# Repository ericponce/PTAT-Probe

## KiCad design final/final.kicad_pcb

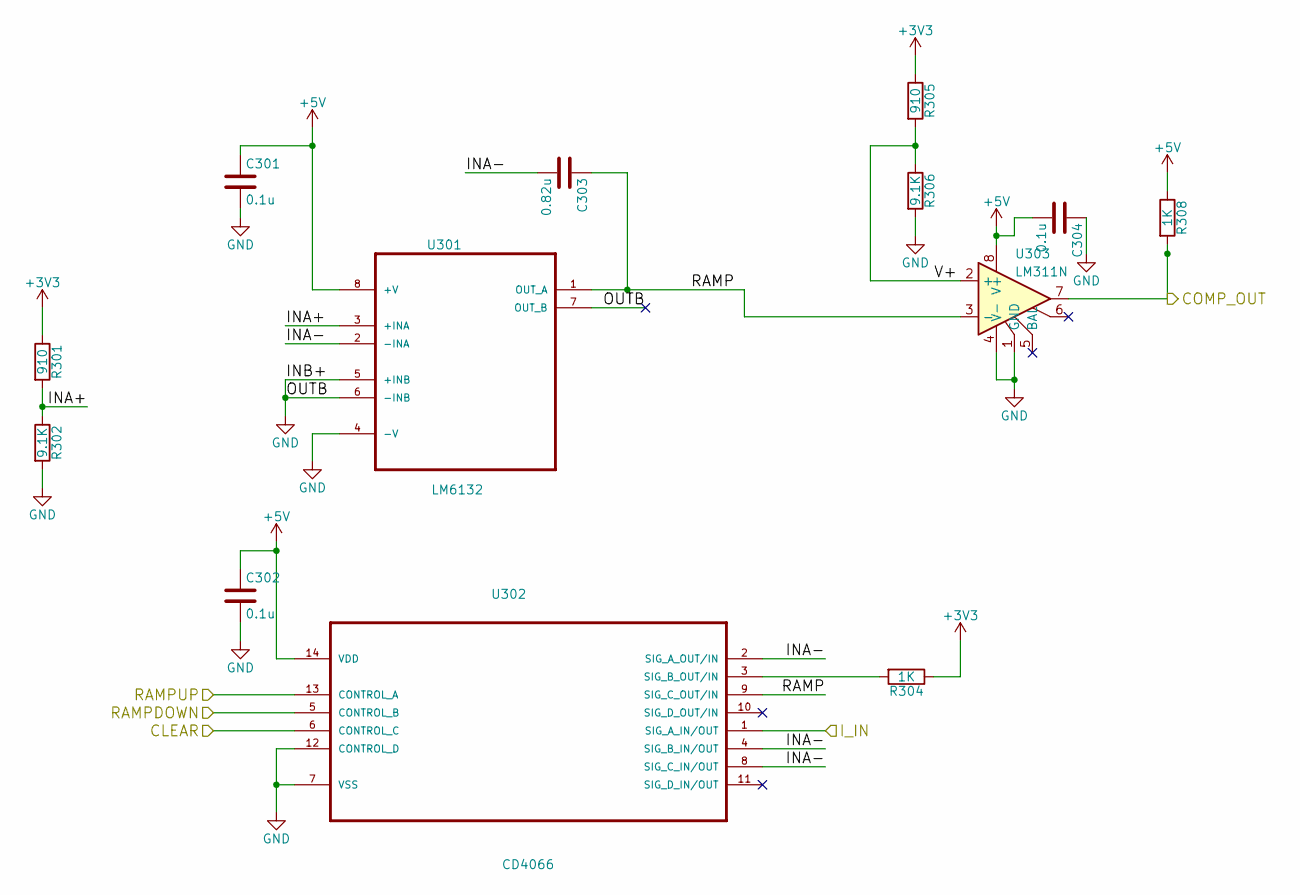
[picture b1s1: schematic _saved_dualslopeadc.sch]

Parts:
C301, C302, C304: 0.1u; C_Rect_L4_W2.5_P2.5
C303: 0.82u; C_Rect_L4_W2.5_P2.5
R301, R305: 910; Resistor_Vertical_RM5mm
R302, R306: 9.1K; Resistor_Vertical_RM5mm
R304, R308: 1K; Resistor_Vertical_RM5mm
U301: LM6132; dil_8-300
U302: CD4066; dil_14-300
U303: LM311N; dil_8-300

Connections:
+3V3: R301.1, R304.1, R305.1; also elsewhere on the board
+5V: C301.1, C302.1, C304.2, R308.1, U301.8 (+V), U302.14 (VDD), U303.8 (V+); also elsewhere on the board
/dualslopeadc/CLEAR: U302.6 (CONTROL_C); also elsewhere on the board
/dualslopeadc/INA+: R301.2, R302.1, U301.3 (+INA)
/dualslopeadc/INA-: C303.2, U301.2 (-INA), U302.2 (SIG_A_OUT/IN), U302.4 (SIG_B_IN/OUT), U302.8 (SIG_C_IN/OUT)
/dualslopeadc/I_IN: U302.1 (SIG_A_IN/OUT); also elsewhere on the board
/dualslopeadc/RAMP: C303.1, U301.1 (OUT_A), U302.9 (SIG_C_OUT/IN), U303.3 (-)
/dualslopeadc/RAMPDOWN: U302.5 (CONTROL_B); also elsewhere on the board
/dualslopeadc/RAMPUP: U302.13 (CONTROL_A); also elsewhere on the board
/dualslopeadc/V+: R305.2, R306.1, U303.2 (+); also elsewhere on the board
/micro/COMP_IN: R308.2, U303.7; also elsewhere on the board
GND: C301.2, C302.2, C304.1, R302.2, R306.2, U301.4 (-V), U301.5 (+INB), U301.6 (-INB), U301.7 (OUT_B), U302.7 (VSS), U302.12 (CONTROL_D), U303.1 (GND), U303.4 (V-); also elsewhere on the board
unnamed: R304.2, U302.3 (SIG_B_OUT/IN)

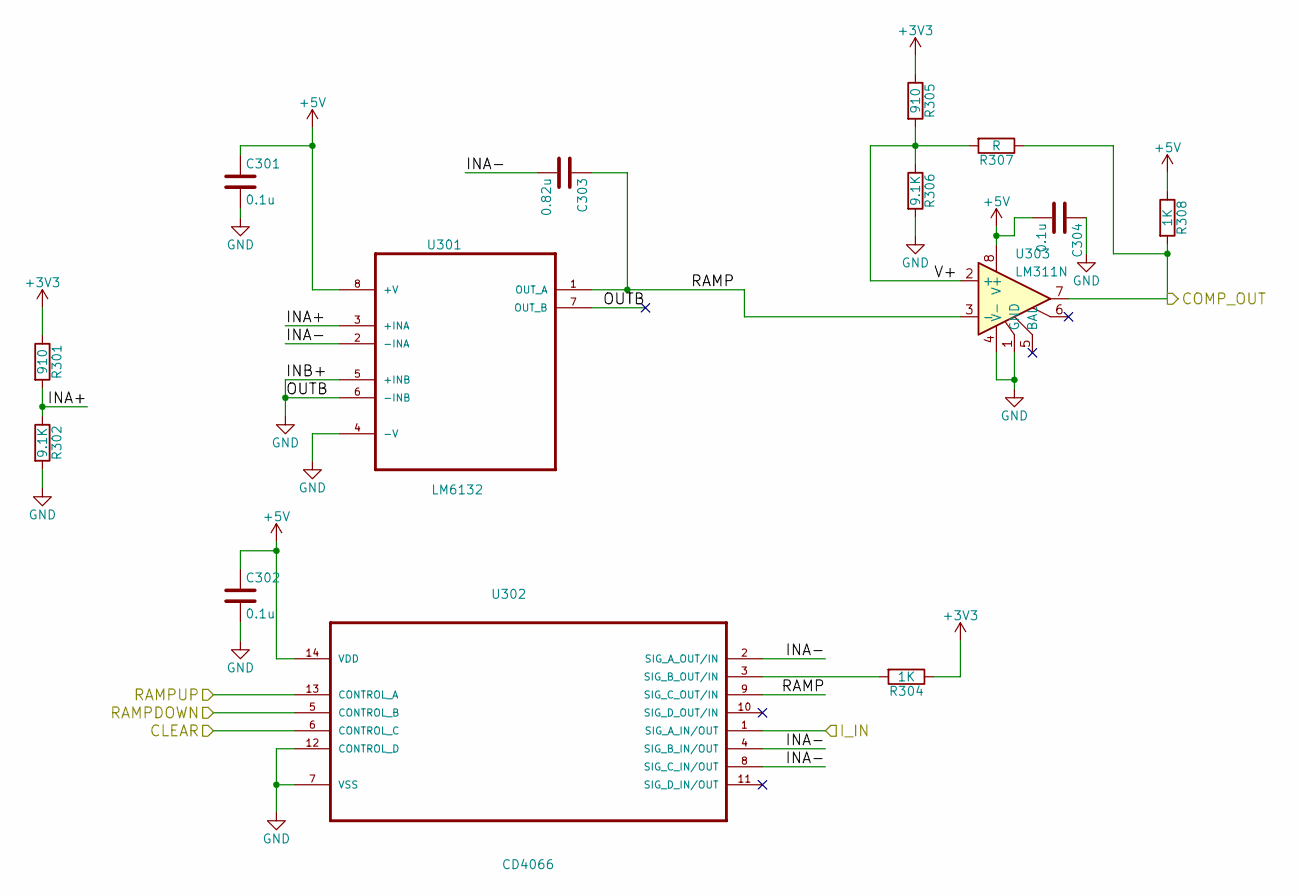
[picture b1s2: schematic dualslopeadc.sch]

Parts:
C301, C302, C304: 0.1u; C_Rect_L4_W2.5_P2.5
C303: 0.82u; C_Rect_L4_W2.5_P2.5
R301, R305: 910; Resistor_Vertical_RM5mm
R302, R306: 9.1K; Resistor_Vertical_RM5mm
R304, R308: 1K; Resistor_Vertical_RM5mm
R307: R; Resistor_Vertical_RM5mm
U301: LM6132; dil_8-300
U302: CD4066; dil_14-300
U303: LM311N; dil_8-300

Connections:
+3V3: R301.1, R304.1, R305.1; also elsewhere on the board
+5V: C301.1, C302.1, C304.2, R308.1, U301.8 (+V), U302.14 (VDD), U303.8 (V+); also elsewhere on the board
/dualslopeadc/CLEAR: U302.6 (CONTROL_C); also elsewhere on the board
/dualslopeadc/INA+: R301.2, R302.1, U301.3 (+INA)
/dualslopeadc/INA-: C303.2, U301.2 (-INA), U302.2 (SIG_A_OUT/IN), U302.4 (SIG_B_IN/OUT), U302.8 (SIG_C_IN/OUT)
/dualslopeadc/I_IN: U302.1 (SIG_A_IN/OUT); also elsewhere on the board
/dualslopeadc/RAMP: C303.1, U301.1 (OUT_A), U302.9 (SIG_C_OUT/IN), U303.3 (-)
/dualslopeadc/RAMPDOWN: U302.5 (CONTROL_B); also elsewhere on the board
/dualslopeadc/RAMPUP: U302.13 (CONTROL_A); also elsewhere on the board
/dualslopeadc/V+: R305.2, R306.1, R307.2, U303.2 (+)
/micro/COMP_IN: R307.1, R308.2, U303.7; also elsewhere on the board
GND: C301.2, C302.2, C304.1, R302.2, R306.2, U301.4 (-V), U301.5 (+INB), U301.6 (-INB), U301.7 (OUT_B), U302.7 (VSS), U302.12 (CONTROL_D), U303.1 (GND), U303.4 (V-); also elsewhere on the board
unnamed: R304.2, U302.3 (SIG_B_OUT/IN)

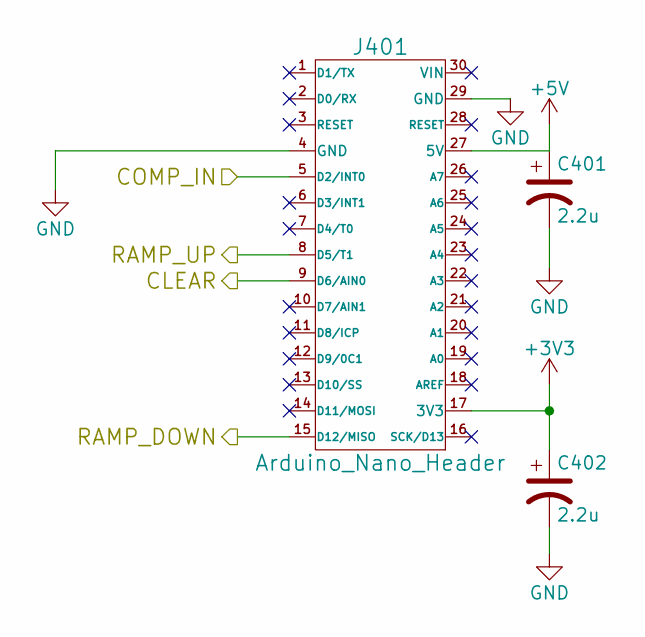
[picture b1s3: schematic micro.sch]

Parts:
C401, C402: 2.2u; C_Radial_D5_L11_P2
J401: Arduino_Nano_Header; arduino_nano_header

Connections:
+3V3: C402.1, J401.17 (3V3); also elsewhere on the board
+5V: C401.1, J401.27 (5V); also elsewhere on the board
/dualslopeadc/CLEAR: J401.9 (D6/AIN0); also elsewhere on the board
/dualslopeadc/RAMPDOWN: J401.15 (D12/MISO); also elsewhere on the board
/dualslopeadc/RAMPUP: J401.8 (D5/T1); also elsewhere on the board
/micro/COMP_IN: J401.5 (D2/INT0); also elsewhere on the board
GND: C401.2, C402.2, J401.4 (GND), J401.29 (GND); also elsewhere on the board

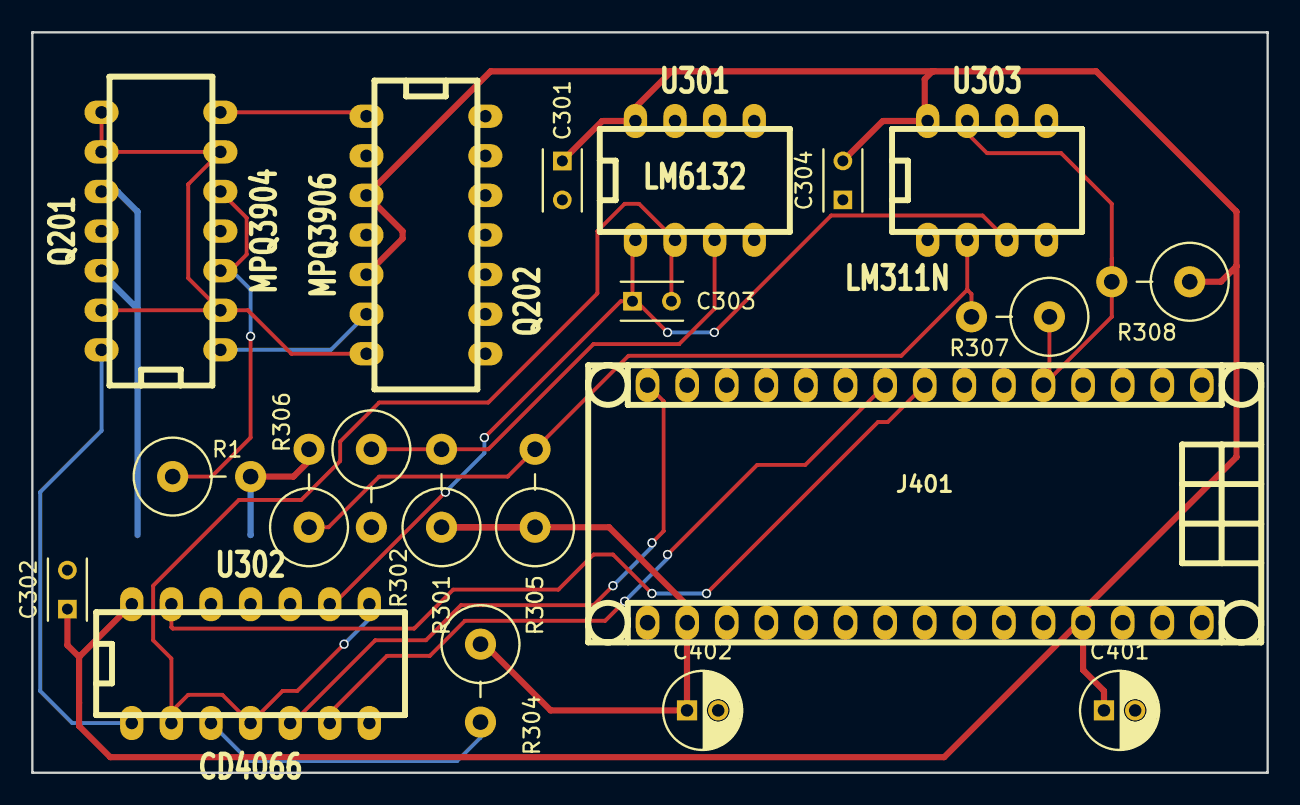
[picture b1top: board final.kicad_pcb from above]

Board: 2 copper layers, 79.2 x 47.5 mm, 20 parts (0 on the bottom side), 16 nets.

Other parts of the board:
Q201: MPQ3904; dil_14-300
Q202: MPQ3906; dil_14-300
R1: 91; Resistor_Vertical_RM5mm

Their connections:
+5V: Q202.3, Q202.5; also elsewhere on the board
/dualslopeadc/I_IN: Q201.14; also elsewhere on the board
GND: Q201.10, Q201.12, R1.2; also elsewhere on the board
unnamed: Q201.1, Q201.7, Q202.1, Q202.2, Q202.6
unnamed: Q201.3, Q201.5, R1.1
unnamed: Q201.2, Q201.6, Q201.8, Q201.9, Q201.13, Q202.7
